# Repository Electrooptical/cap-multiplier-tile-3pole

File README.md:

# Capacitance Multiplier Board
This is a 3-pole capacitance multiplier board for use with low noise instruments.
You sacrifice about a volt but get an incredibly quiet power supply.
This layout is intended to be used as a module and soldered to a target board using the castellated holes.

+ 3 Pole power supply filtering
+ Bipolar supplies up to +-20V. 
+ Reverse polarity protection
+ Extreme rejection of switch mode power supply frequencies

Used in our:

+ Low noise amplifiers
+ High gain photoreceivers
+ Low noise laser drivers

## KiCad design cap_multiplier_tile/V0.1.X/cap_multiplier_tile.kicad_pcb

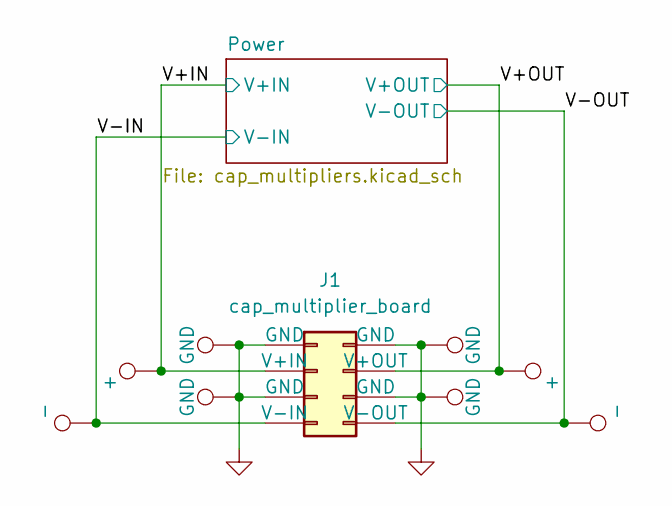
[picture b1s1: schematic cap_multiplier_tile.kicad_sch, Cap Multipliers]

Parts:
J1: cap_multiplier_board; board
TP1, TP7: +; TestPoint_Pad_D1.0mm
TP2, TP8: -; TestPoint_Pad_D1.0mm
TP3, TP4, TP5, TP6: GND; TestPoint_Pad_D1.0mm

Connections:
/V+IN: J1.2 (V+IN), TP7.1; also elsewhere on the board
/V+OUT: J1.7 (V+OUT), TP1.1; also elsewhere on the board
/V-IN: J1.4 (V-IN), TP8.1; also elsewhere on the board
/V-OUT: J1.5 (V-OUT), TP2.1; also elsewhere on the board
GND: J1.1 (GND), J1.3 (GND), J1.6 (GND), J1.8 (GND), TP3.1, TP4.1, TP5.1, TP6.1; also elsewhere on the board

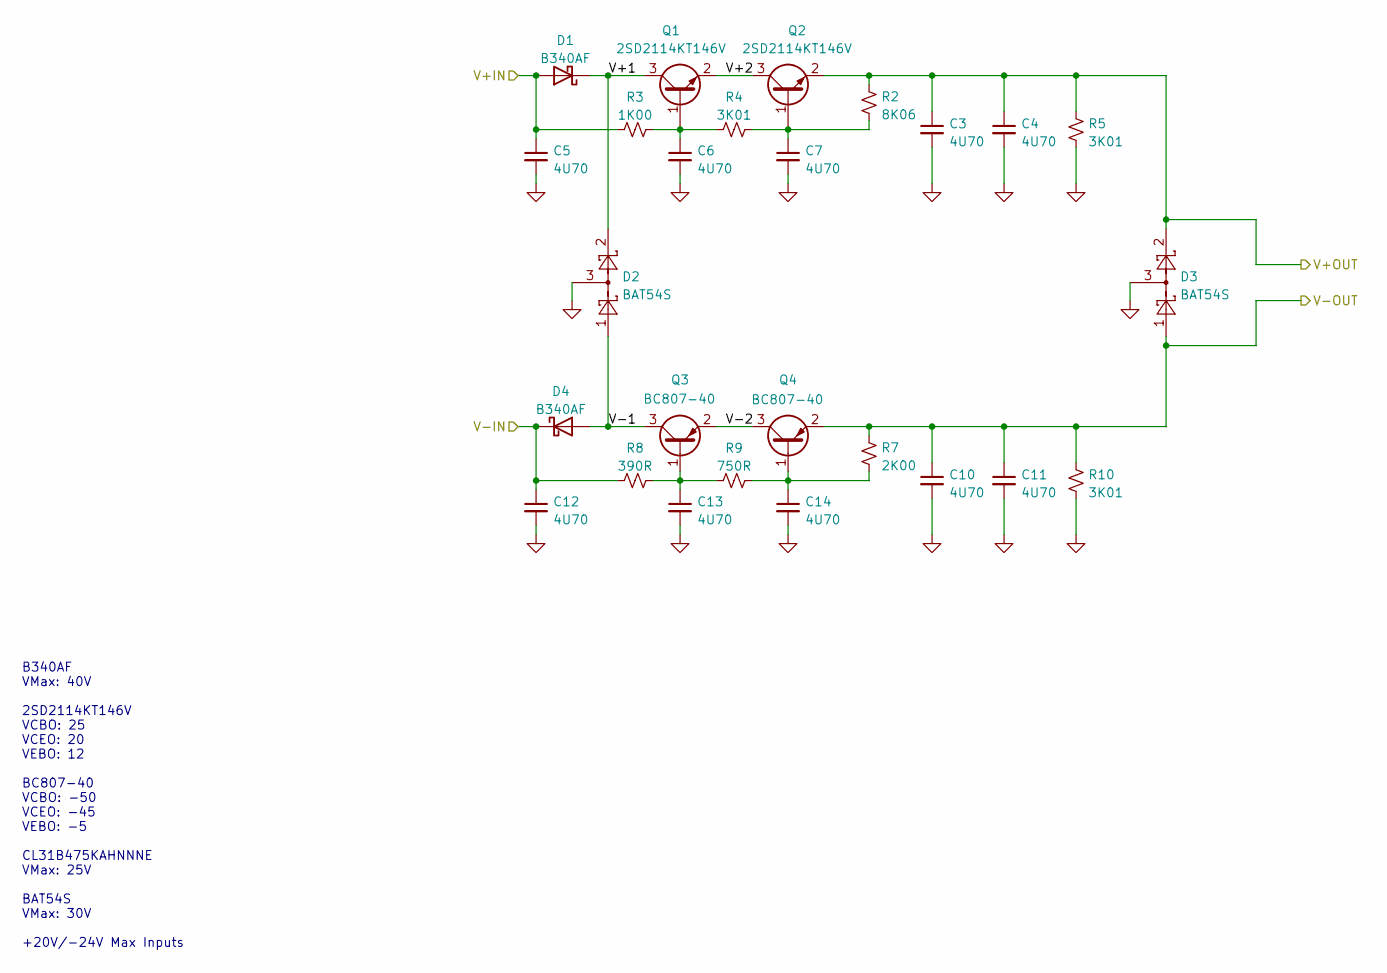
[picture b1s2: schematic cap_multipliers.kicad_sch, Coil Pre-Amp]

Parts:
C3, C4, C5, C6, C7, C10, C11, C12, C13, C14: 4U70; C_1206_3216Metric; LCSC C1872
D1, D4: B340AF; D_SMA; LCSC C85098
D2, D3: BAT54S; SOT-23; LCSC C377935
Q1, Q2: 2SD2114KT146V; SOT-23; LCSC C308659
Q3, Q4: BC807-40; SOT-23; LCSC C57316
R2: 8K06; R_0402_1005Metric
R3: 1K00; R_0402_1005Metric
R4, R5, R10: 3K01; R_0402_1005Metric
R7: 2K00; R_0402_1005Metric
R8: 390R; R_0402_1005Metric
R9: 750R; R_0402_1005Metric

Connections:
/Power/V+1: D1.1 (K), D2.2 (K), Q1.3 (C)
/Power/V+2: Q1.2 (E), Q2.3 (C)
/Power/V-1: D2.1 (A), D4.2 (A), Q3.3 (C)
/Power/V-2: Q3.2 (E), Q4.3 (C)
/V+IN: C5.1, D1.2 (A), R3.1; also elsewhere on the board
/V+OUT: C3.1, C4.1, D3.2 (K), Q2.2 (E), R2.2, R5.2; also elsewhere on the board
/V-IN: C12.1, D4.1 (K), R8.1; also elsewhere on the board
/V-OUT: C10.1, C11.1, D3.1 (A), Q4.2 (E), R7.2, R10.2; also elsewhere on the board
GND: C3.2, C4.2, C5.2, C6.2, C7.2, C10.2, C11.2, C12.2, C13.2, C14.2, D2.3 (COM), D3.3 (COM), R5.1, R10.1; also elsewhere on the board
unnamed: C6.1, Q1.1 (B), R3.2, R4.1
unnamed: C7.1, Q2.1 (B), R2.1, R4.2
unnamed: C13.1, Q3.1 (B), R8.2, R9.1
unnamed: C14.1, Q4.1 (B), R7.1, R9.2

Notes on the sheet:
B340AF VMax: 40V 2SD2114KT146V VCBO: 25 VCEO: 20 VEBO: 12 BC807-40 VCBO: -50 VCEO: -45 VEBO: -5 CL31B475KAHNNNE VMax: 25V BAT54S VMax: 30V +20V/-24V Max Inputs

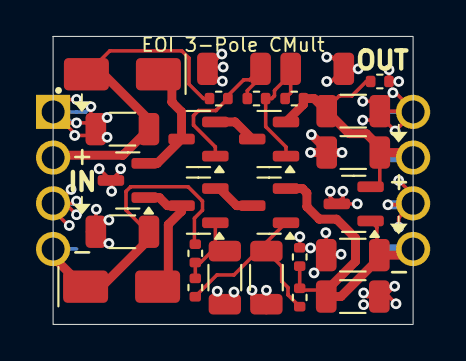
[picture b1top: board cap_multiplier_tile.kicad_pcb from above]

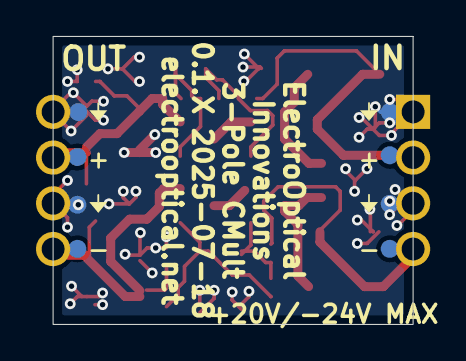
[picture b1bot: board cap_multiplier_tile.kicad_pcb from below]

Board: 2 copper layers, 20.0 x 16.0 mm, 35 parts (8 on the bottom side), 13 nets.

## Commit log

2025-07-21 adding transistor symbols
2025-08-06 adding action, removing library dependancy
2025-08-06 adding action
